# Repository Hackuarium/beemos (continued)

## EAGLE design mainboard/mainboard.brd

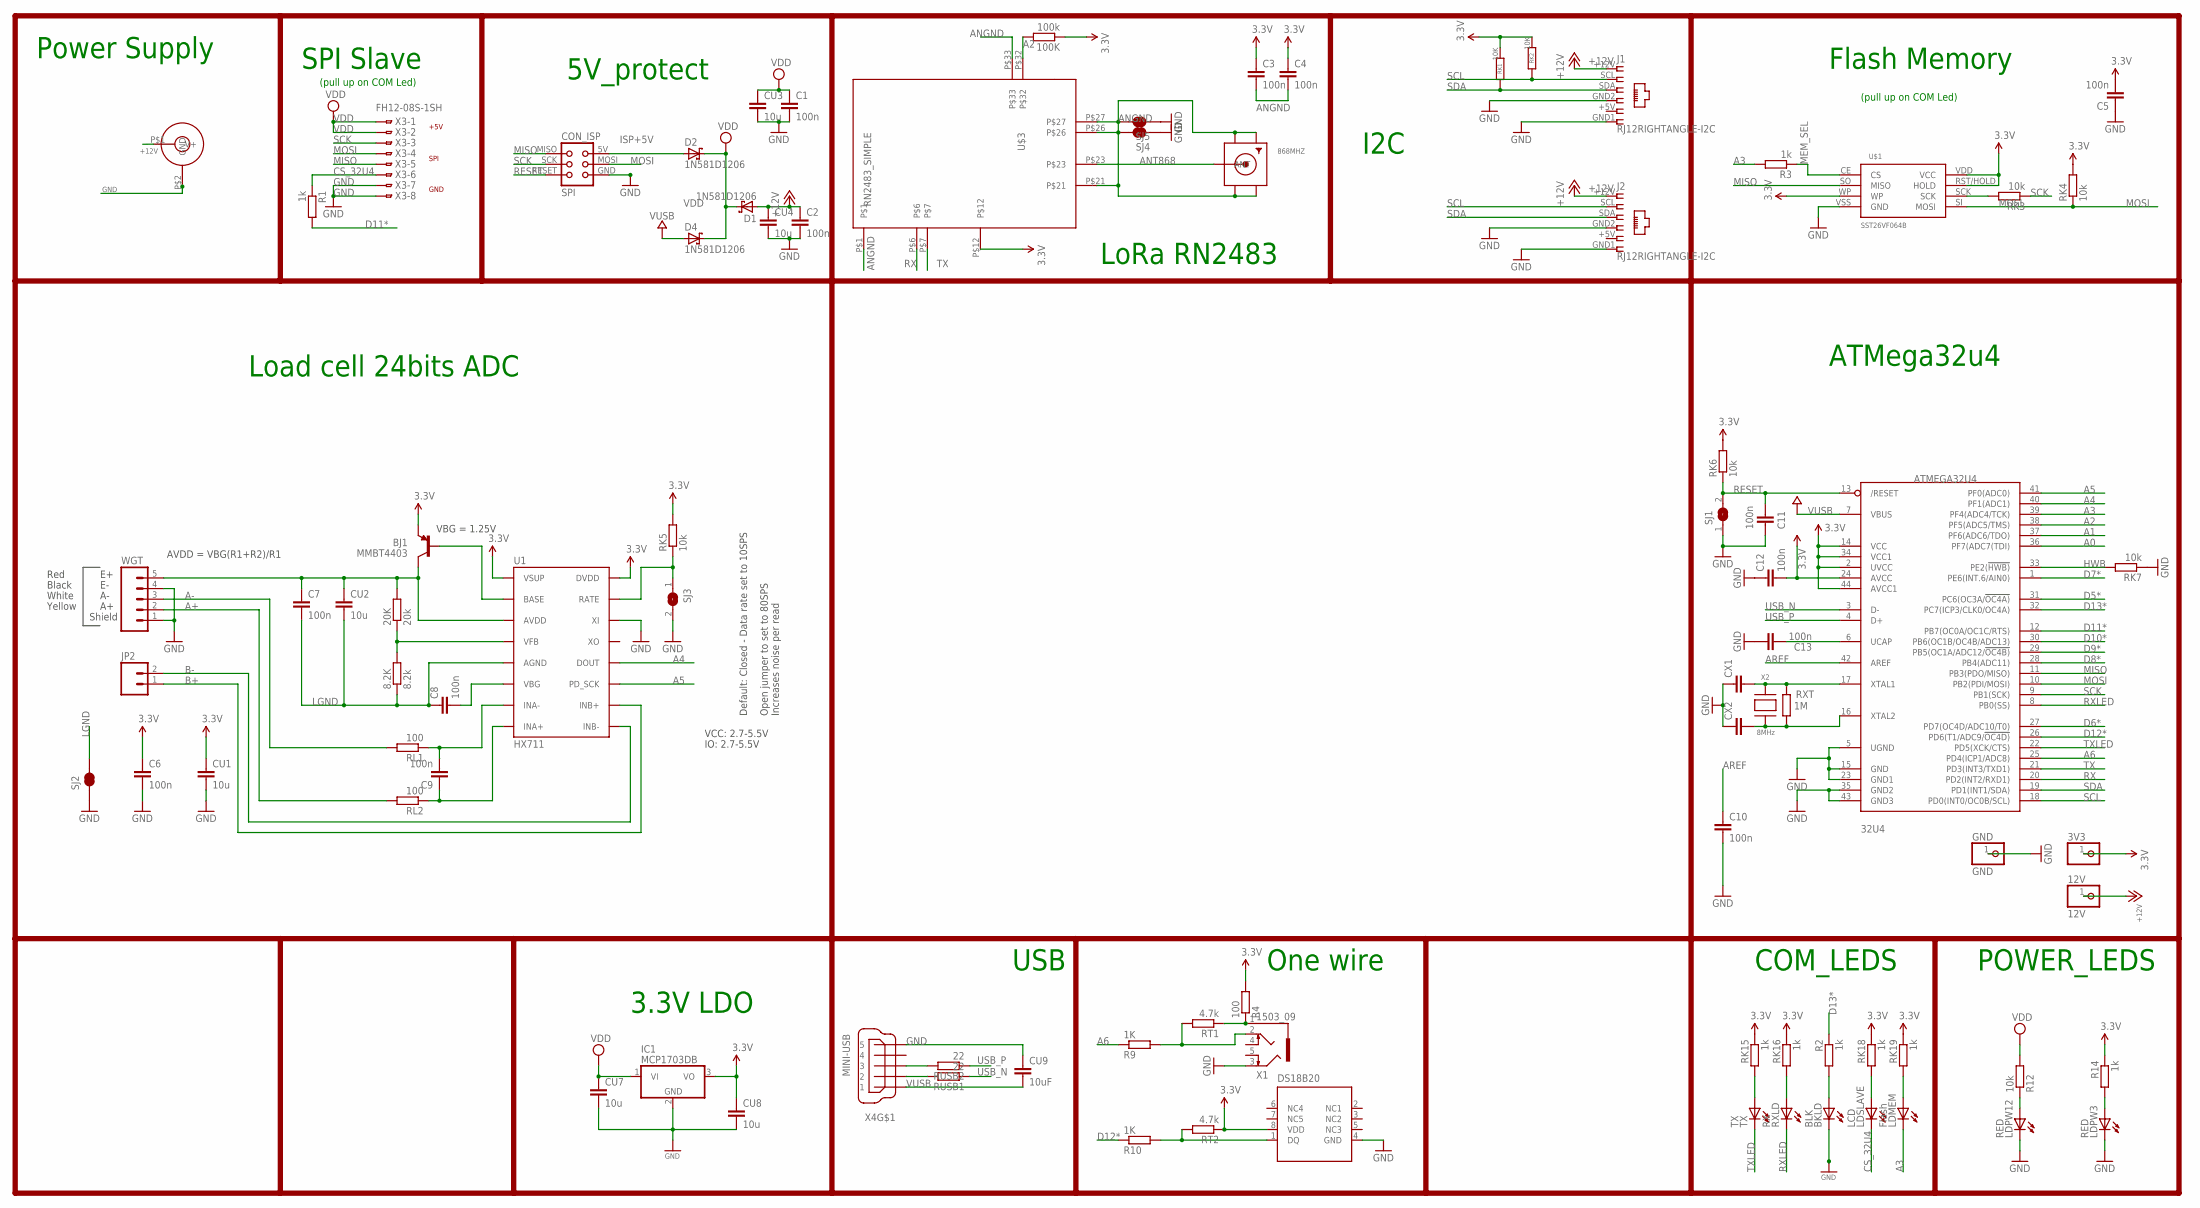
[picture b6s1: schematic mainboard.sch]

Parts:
3V3: PINHD-1X1; 1X01
8.2K: 8.2k; M0805
12V: 12V; 1X01
20K: 20k; M0805
32U4: ATMEGA32U4; TQFP44
100K: 100k; R0805
868MHZ: SMACONNECTOR_EDGE_UFL; SMA_EDGELAUNCH_UFL
BJ1: MMBT4403; SOT23-3
BKLD: BLK; CHIP-LED0805
C1, C2, C3, C4, C5, C6, C7, C8, C9, C10, C11, C12, C13: 100n; C0805
CON1: JACK_DC_BARREL; DC_BARREL
CON_ISP: SPI; TC2030-MCP-NL
CU1, CU2, CU3, CU4, CU7, CU8: 10u; C0805
CU9: 10uF; C0805
CX1, CX2: 22pF; C0805
D1, D2, D4: 1N581D1206; LED-1206
GND: GND; 1X01
IC1: MCP1703DB; SOT223
J1, J2: RJ12RIGHTANGLE-I2C; RJ12-RIGHTANGLE-I2C
JP2: M02PTH; 1X02
LDMEM: Flash; CHIP-LED0805
LDPW3, LDPW12: RED; CHIP-LED0805
LDSLAVE: LCD; CHIP-LED0805
R1, R2, R3, R14: 1k; R0805
R4: 100; R0805
R9, R10: 1K; R0805
R12: 10k; R0805
RK1, RK2: 10K; M0805
RK3, RK4: 10k; R0805
RK5, RK6, RK7: 10k; M0805
RK15, RK16, RK18, RK19: 1k; R0805
RL1, RL2: 100; M0805
RT1, RT2: 4.7k; R0805
RUSB1, RUSB2: 22; M0805
RXLD: RX; CHIP-LED0805
RXT: 1M; R0805
SJ1, SJ3: SJ
SJ2, SJ4, SJ5: JUMPER-PAD-2-NC_BY_TRACE; PAD-JUMPER-2-NC_BY_TRACE_YES_SILK
TX: TX; CHIP-LED0805
U1: HX711; SO16
U$1: SST26VF064B; SOIC_8-LEAD
U$2: DS18B20; MSOP8
U$3: RN2483_SIMPLE
WGT: M05PTH; 1X05
X1: 1503_09
X2: 8MHz; NX6035
X3: FH12-08S-1SH
X4: MINI-USB; 32005-201

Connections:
3.3V: 3V3.1, 32U4.2 (UVCC), 32U4.14 (VCC), 32U4.24 (AVCC), 32U4.34 (VCC1), 32U4.44 (AVCC1), 100K.1, BJ1.2 (E), C3.1, C4.1, C5.2, C6.1, C12.2, CU1.1, CU8.1, IC1.3 (VO), R4.2, R14.1, RK1.1, RK2.1, RK4.2, RK5.2, RK6.2, RK15.1, RK16.1, RK18.1, RK19.1, RT2.1, U1.1 (VSUP), U1.16 (DVDD), U$1.RST/HOLD (HOLD), U$1.VDD (VCC), U$1.WP, U$2.8 (VDD), U$3.P$12
5: J1.+5V (5), J2.+5V (5)
+12V: 12V.1, C2.1, CON1.P$1 (V+), CU4.1, D1.A, J1.+12V (1), J2.+12V (1)
A0: 32U4.36 (PF7(ADC7(TDI))
A1: 32U4.37 (PF6(ADC6/TDO))
A2: 32U4.38 (PF5(ADC5/TMS)), 100K.2, U$3.P$32
A3: 32U4.39 (PF4(ADC4/TCK)), LDMEM.C, R3.2
A4: 32U4.40 (PF1(ADC1)), U1.12 (DOUT)
A5: 32U4.41 (PF0(ADC0)), U1.11 (PD_SCK)
A6: 32U4.25 (PD4(ICP1/ADC8)), R9.1
A+: RL2.2, WGT.2
A-: RL1.2, WGT.3
ANGND: 868MHZ.GND@1 (GND1), 868MHZ.GND@2 (GND2), 868MHZ.GND@3 (GND3), 868MHZ.GND@4 (GND4), C3.2, C4.2, SJ4.2, SJ5.2, U$3.P$1, U$3.P$21, U$3.P$26, U$3.P$27, U$3.P$33
ANT868: 868MHZ.P (ANT), U$3.P$23
AREF: 32U4.42 (AREF), C10.1
B+: JP2.1, U1.10 (INB+)
B-: JP2.2, U1.9 (INB-)
CN3: C8.2, U1.6 (VBG)
CS_32U4: LDSLAVE.C, R1.1, X3.6
D5*: 32U4.31 (PC6(OC3A/!OC4A))
D6*: 32U4.27 (PD7(OC4D/ADC10/T0))
D7*: 32U4.1 (PE6(INT.6/AIN0))
D8*: 32U4.28 (PB4(ADC11))
D9*: 32U4.29 (PB5(OC1A/ADC12/!OC4B))
D10*: 32U4.30 (PB6(OC1B/OC4B/ADC13))
D11*: 32U4.12 (PB7(OC0A/OC1C/RTS)), R1.2
D12*: 32U4.26 (PD6(T1/ADC9/!OC4D)), R10.1
D13*: 32U4.32 (PC7(ICP3/CLK0/OC4A)), R2.1
GND: 32U4.5 (UGND), 32U4.15 (GND), 32U4.23 (GND1), 32U4.35 (GND2), 32U4.43 (GND3), BKLD.C, C1.2, C2.2, C5.1, C6.2, C10.2, C11.2, C12.1, C13.1, CON1.P$2 (GND), CON_ISP.GND, CU1.2, CU3.2, CU4.2, CU7.2, CU8.2, CU9.1, CX1.1, CX2.1, GND.1, IC1.2 (GND), J1.GND1 (6), J1.GND2 (4), J2.GND1 (6), J2.GND2 (4), LDPW3.C, LDPW12.C, RK7.1, SJ1.1, SJ2.1, SJ3.2, SJ4.1, SJ5.1, U1.14 (XI), U$1.VSS (GND), U$2.4 (GND), WGT.1, WGT.4, X1.3, X3.7, X3.8, X4.5
HWB: 32U4.33 (PE2(!HWB)), RK7.2
ISP+5V: CON_ISP.5V (VCC), D2.A
LGND: 8.2K.1, C7.2, C8.1, CU2.2, SJ2.2, U1.5 (AGND)
MEM_SEL: R3.1, U$1.CE (CS)
MISO: 32U4.11 (PB3(PDO/MISO)), CON_ISP.MISO, U$1.SO (MISO), X3.5
MOSI: 32U4.10 (PB2(PDI/MOSI)), CON_ISP.MOSI, RK4.1, U$1.SI (MOSI), X3.4
unnamed: 32U4.6 (UCAP), C13.2
unnamed: BKLD.A, R2.2
unnamed: 20K.2, BJ1.3 (C), C7.1, CU2.1, U1.3 (AVDD), WGT.5
unnamed: LDPW12.A, R12.1
unnamed: R10.2, RT2.2, U$2.1 (DQ)
unnamed: R4.1, RT1.1, X1.1
unnamed: RK15.2, TX.A
unnamed: C9.2, RL1.1, U1.7 (INA-)
unnamed: R9.2, RT1.2, X1.2
unnamed: LDSLAVE.A, RK18.2
unnamed: RK3.2, U$1.SCK
unnamed: RK16.2, RXLD.A
unnamed: LDMEM.A, RK19.2
unnamed: LDPW3.A, R14.2
unnamed: BJ1.1 (B), U1.2 (BASE)
unnamed: 8.2K.2, 20K.1, U1.4 (VFB)
unnamed: RK5.1, SJ3.1, U1.15 (RATE)
unnamed: 32U4.17 (XTAL1), CX1.2, RXT.2, X2.P$2
unnamed: C9.1, RL2.1, U1.8 (INA+)
RESET: 32U4.13 (/RESET), C11.1, CON_ISP.RESET, RK6.1, SJ1.2
RX: 32U4.20 (PD2(INT2/RXD1)), U$3.P$6
RXLED: 32U4.8 (PB0(SS)), RXLD.C
SCK: 32U4.9 (PB1(SCK)), CON_ISP.SCK, RK3.1, X3.3
SCL: 32U4.18 (PD0(INT0/OC0B/SCL)), J1.SCL (2), J2.SCL (2), RK2.2
SDA: 32U4.19 (PD1(INT1/SDA)), J1.SDA (3), J2.SDA (3), RK1.2
TX: 32U4.21 (PD3(INT3/TXD1)), U$3.P$7
TXLED: 32U4.22 (PD5(XCK/CTS)), TX.C
USBC_N: RUSB1.2, X4.2
USBC_P: RUSB2.2, X4.3
USB_N: 32U4.3 (D-), RUSB1.1
USB_P: 32U4.4 (D+), RUSB2.1
VDD: C1.1, CU3.1, CU7.1, D1.C, D2.C, D4.C, IC1.1 (VI), R12.2, X3.1, X3.2
VUSB: 32U4.7 (VBUS), CU9.2, D4.A, X4.1
XTAL1: 32U4.16 (XTAL2), CX2.2, RXT.1, X2.P$1

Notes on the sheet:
Flash Memory
USB
Power Supply
LoRa RN2483
One wire
I2C
5V_protect
POWER_LEDS
COM_LEDS
3.3V LDO
VCC: 2.7-5.5V
VBG = 1.25V
AVDD = VBG(R1+R2)/R1
Default: Closed - Data rate set to 10SPS
Open jumper to set to 80SPS Increases noise per read
Red
Black
White
IO: 2.7-5.5V
Shield
Yellow
ATMega32u4
Load cell 24bits ADC
SPI Slave
GND
+5V
SPI
(pull up on COM Led)

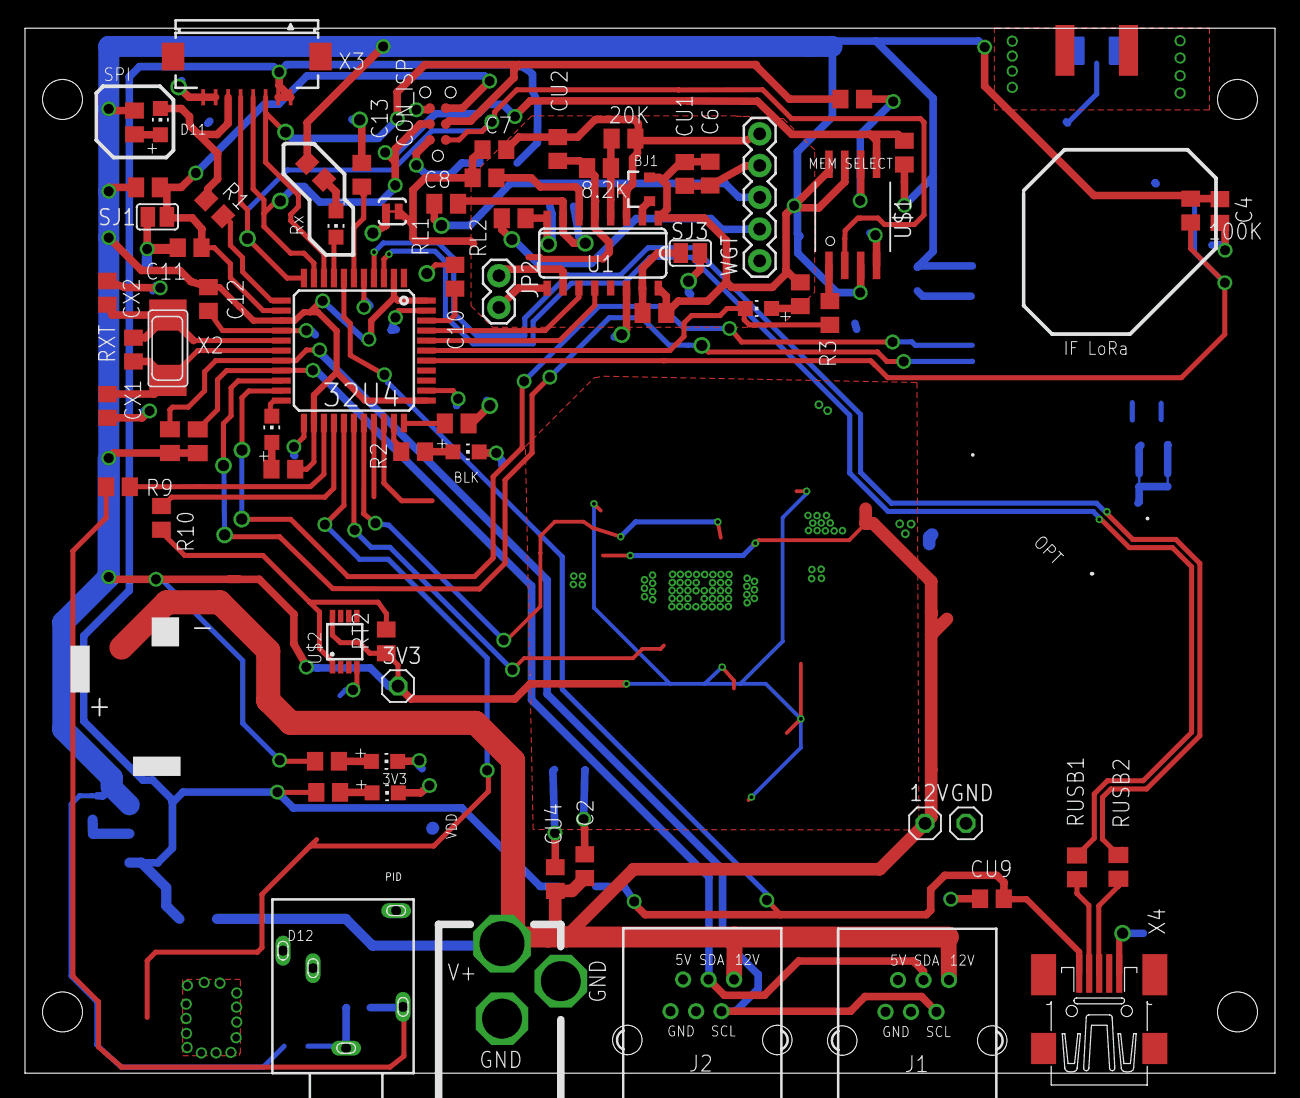
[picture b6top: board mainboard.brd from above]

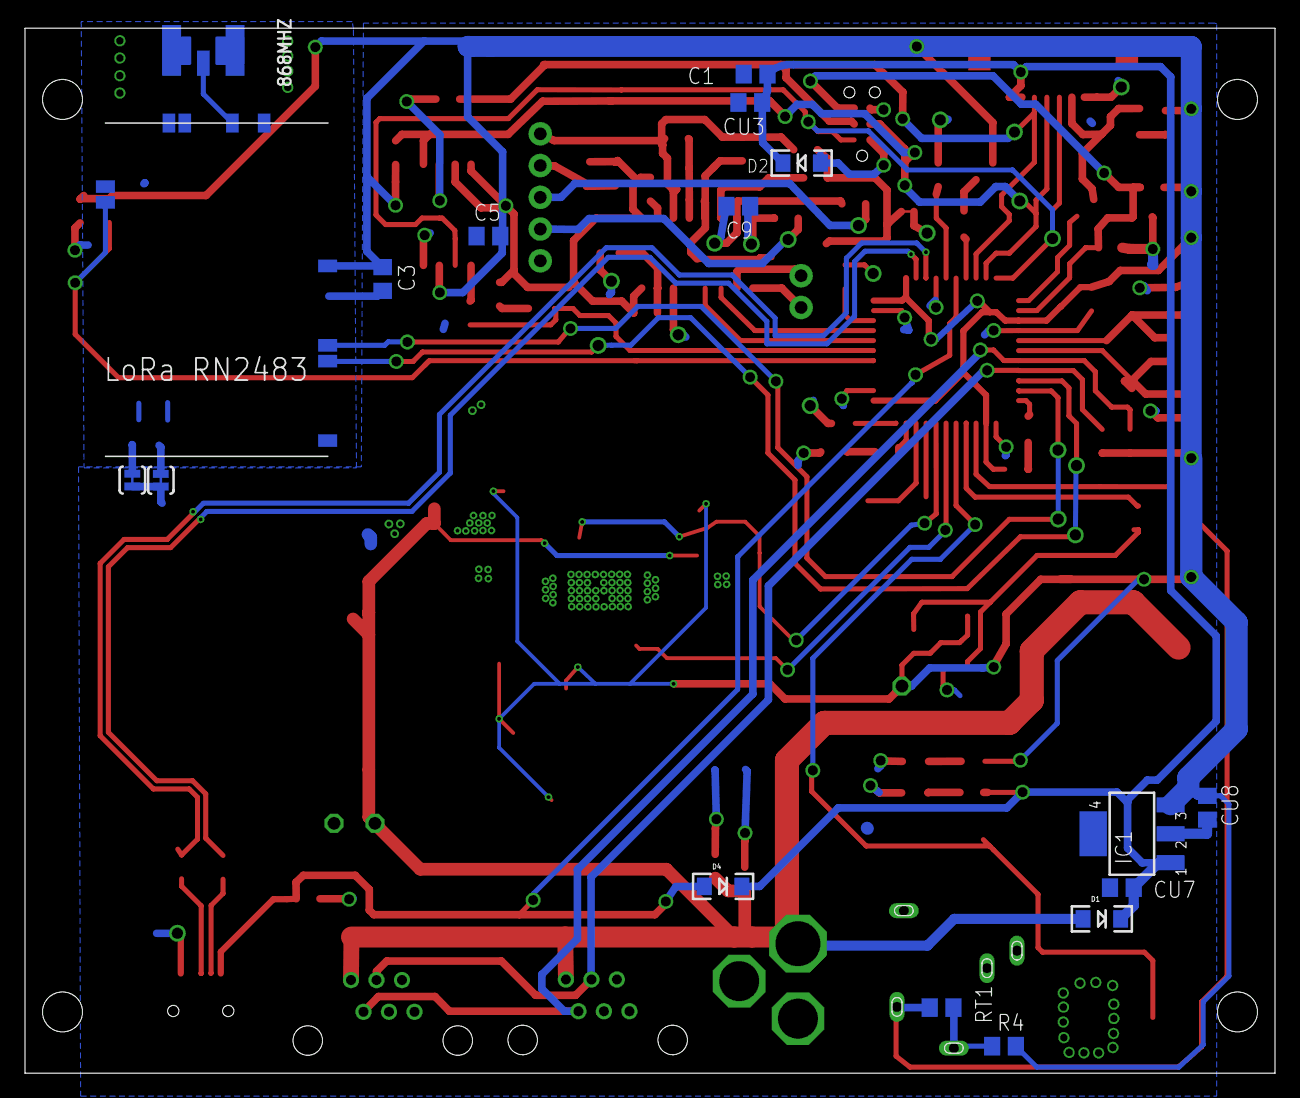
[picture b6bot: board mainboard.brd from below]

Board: 4 copper layers, 100.0 x 83.6 mm, 87 parts (17 on the bottom side), 61 nets.
